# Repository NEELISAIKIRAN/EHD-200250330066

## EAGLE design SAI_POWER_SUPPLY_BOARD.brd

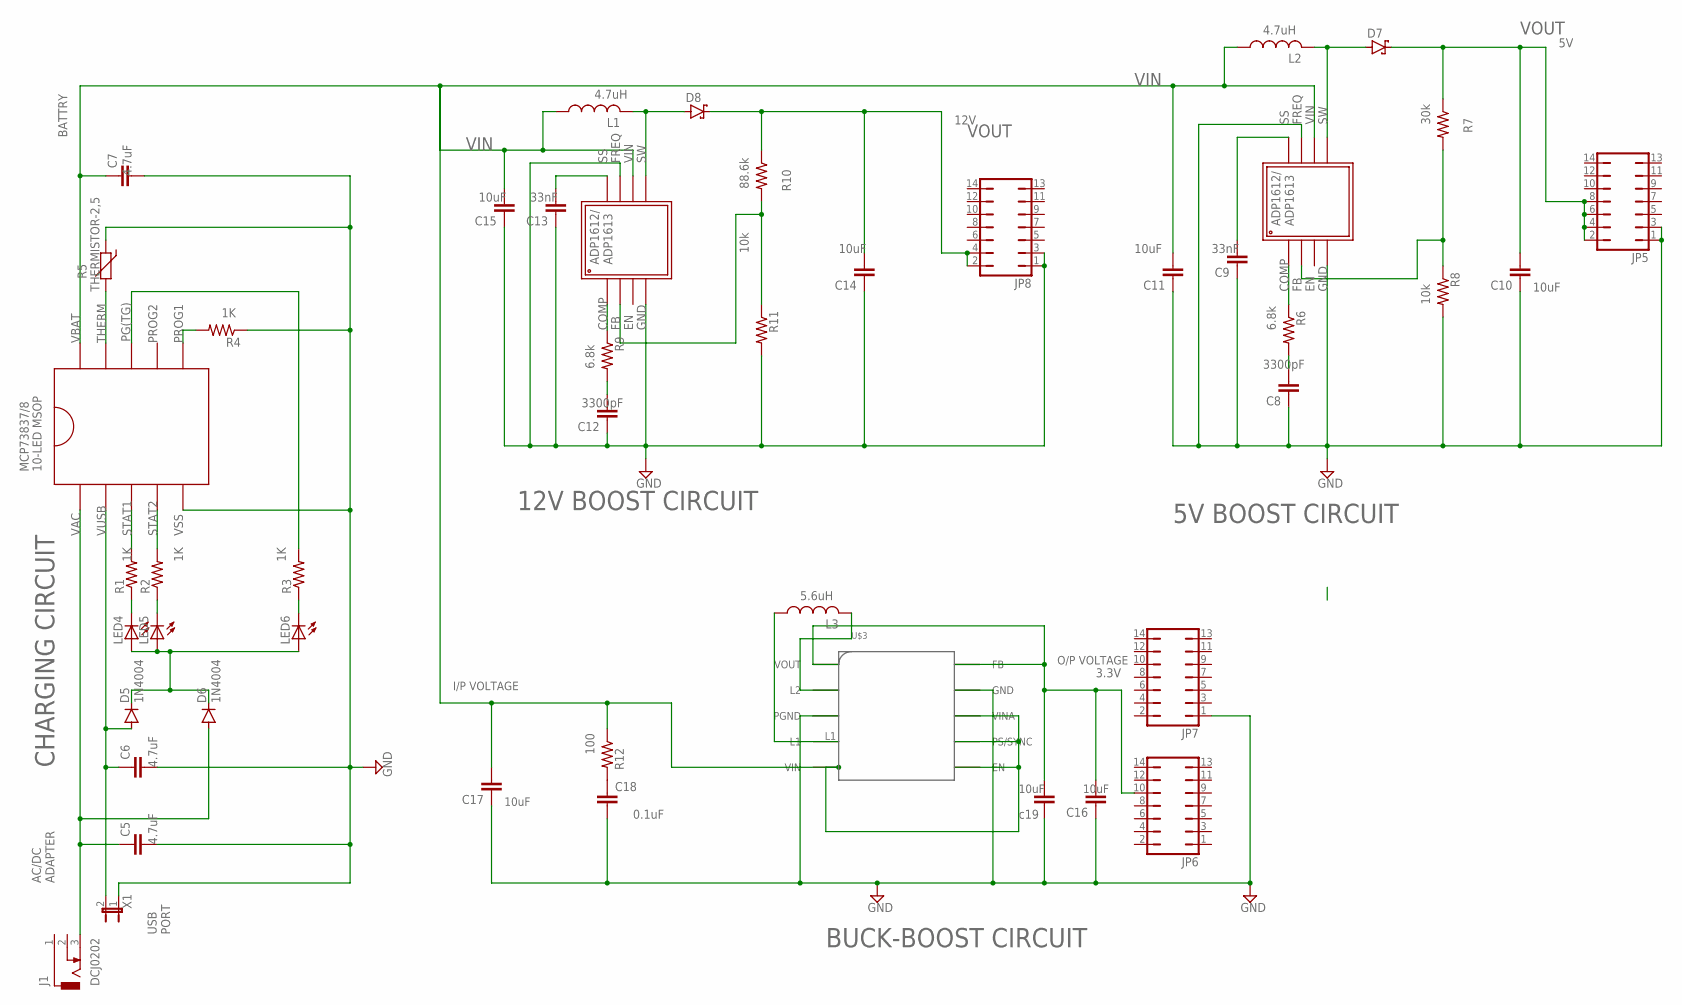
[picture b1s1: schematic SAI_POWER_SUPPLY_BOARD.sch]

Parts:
C1, C8, C9, C10, C11, C12, C13, C14, C15, C16, C17, C18: C2,5-3; C2.5-3
C5, C6, C7: C2.5/5; C2.5-5
D5, D6: 1N4004; DO41-10
D7, D8: SCHOTTKY-DIODEC4111-15; C4111-15
J1: DCJ0202
JP1: JP1E; JP1
JP5, JP6, JP7, JP8: JP7Q
L1, L2, L3: L-US0204/5; 0204/5
LED4, LED5, LED6: LED3MM
R1, R2, R3, R4, R6, R7, R8, R9, R10, R11, R12: R-US_0204/2V; 0204V
R5: THERMISTOR-2,5; RS-2,5
U$1, U$2: ADP1612
U$3: TPS63002
U$4: MCP73837/8

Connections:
GND: C1.1, C5.2, C6.2, C7.2, C8.1, C9.1, C10.1, C11.1, C12.1, C13.1, C14.1, C15.1, C16.1, C17.1, C18.2, JP1.1, JP5.1, JP5.3, JP7.1, JP8.1, JP8.3, R4.1, R5.1, R8.2, R11.2, U$1.P$4, U$1.P$6, U$2.P$4, U$2.P$6, U$3.GND, U$3.PGND, U$4.P$5
unnamed: C10.2, D7.C, JP5.2, JP5.4, JP5.6, JP5.8, R7.1
unnamed: L3.1, U$3.L1
unnamed: C7.1, C11.2, C15.2, C17.2, L1.1, L2.1, R12.1, U$1.P$7, U$2.P$7, U$3.EN, U$3.PS/SYNC, U$3.VIN, U$3.VINA, U$4.P$10
unnamed: C1.2, C16.2, JP6.10, U$3.FB, U$3.VOUT
unnamed: L3.2, U$3.L2
unnamed: C18.1, R12.2
unnamed: C5.1, D6.A, J1.3, U$4.P$1
unnamed: C14.2, D8.C, JP8.2, JP8.4, R10.1
unnamed: C6.1, D5.A, JP1.2, U$4.P$2
unnamed: D5.C, D6.C, LED4.A, LED5.A, LED6.A
unnamed: R4.2, U$4.P$6
unnamed: R5.2, U$4.P$9
unnamed: LED4.K (C), R1.1
unnamed: R1.2, U$4.P$3
unnamed: R2.2, U$4.P$4
unnamed: LED5.K (C), R2.1
unnamed: LED6.K (C), R3.1
unnamed: R3.2, U$4.P$8
unnamed: D7.A, L2.2, U$1.P$8
unnamed: R6.1, U$1.P$1
unnamed: C8.2, R6.2
unnamed: R7.2, R8.1, U$1.P$2
unnamed: C9.2, U$1.P$5
unnamed: D8.A, L1.2, U$2.P$8
unnamed: R9.1, U$2.P$1
unnamed: C12.2, R9.2
unnamed: R10.2, R11.1, U$2.P$2
unnamed: C13.2, U$2.P$5

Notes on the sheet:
AC/DC ADAPTER
USB PORT
BATTRY
CHARGING CIRCUIT
VIN
VOUT
5V BOOST CIRCUIT
12V BOOST CIRCUIT
10uF
30k
10k
4.7uH
33nF
6.8k
3300pF
88.6k
BUCK-BOOST CIRCUIT
I/P VOLTAGE
O/P VOLTAGE
5.6uH
c19
3.3V
12V
100
0.1uF
4.7uF

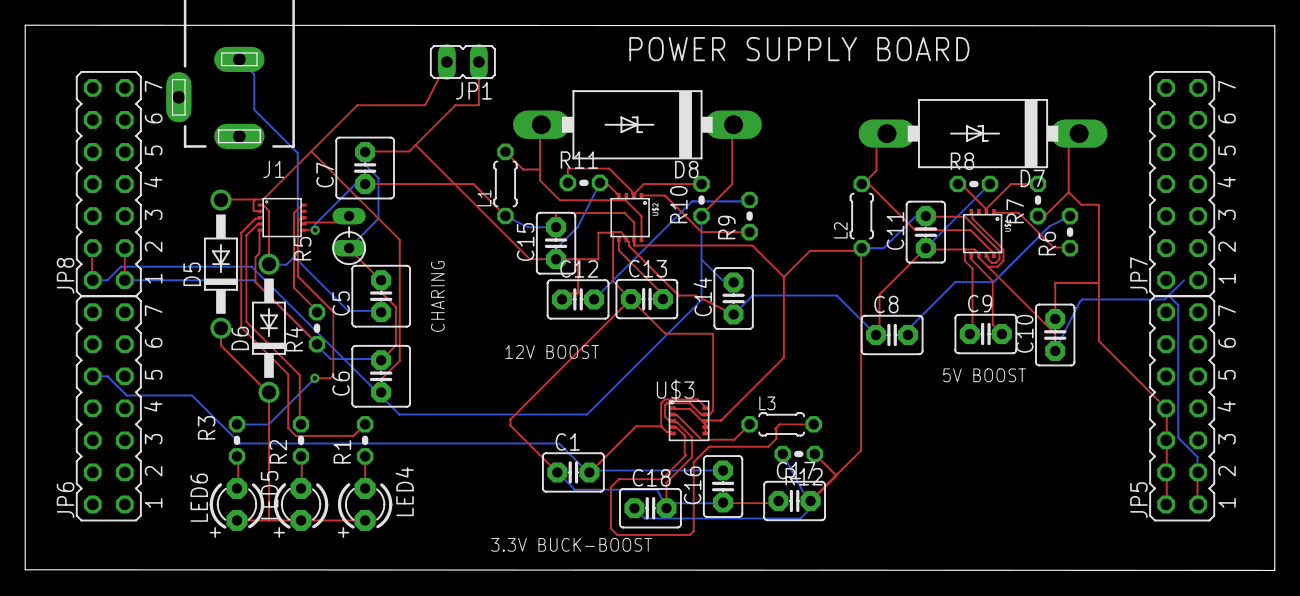
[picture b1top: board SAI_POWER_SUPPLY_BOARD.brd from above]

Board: 2 copper layers, 99.1 x 43.2 mm, 47 parts (0 on the bottom side), 29 nets.

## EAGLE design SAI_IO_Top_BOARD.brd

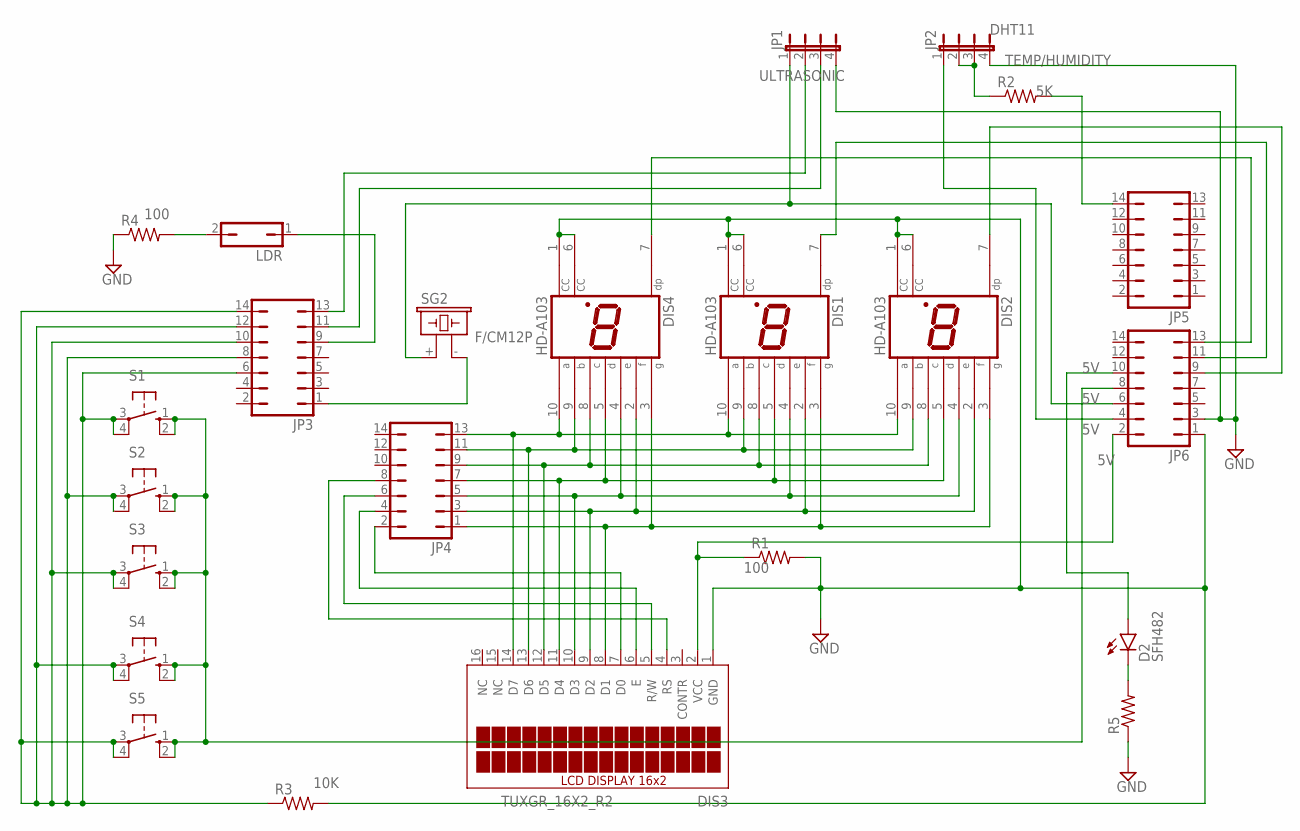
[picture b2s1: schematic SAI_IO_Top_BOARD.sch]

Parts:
D2: SFH482
DIS1, DIS2, DIS4: HD-A103; HDSP-A
DIS3: TUXGR_16X2_R2
JP1, JP2: JP4E; JP4
JP3, JP4, JP5, JP6: JP7Q
LDR: JP1Q; JP1
R1, R2, R3, R4, R5: R-US_0204/2V; 0204V
S1, S2, S3, S4, S5: 10-XX; B3F-10XX
SG2: F/CM12P

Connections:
5V: JP1.1, JP6.6, SG2.+ (1)
GND: DIS1.1 (CC), DIS1.6 (CC), DIS2.1 (CC), DIS2.6 (CC), DIS3.1 (GND), DIS4.1 (CC), DIS4.6 (CC), JP1.4, JP2.4, JP6.1, JP6.3, R1.2, R3.2, R4.1, R5.1; also elsewhere on the board
unnamed: JP3.1, SG2.- (2)
unnamed: JP2.2, JP2.3, R2.1
unnamed 6: DIS1.3 (G), DIS2.3 (G), DIS3.8 (D1), DIS4.3 (G), JP4.1; also elsewhere on the board
unnamed 7: DIS1.2 (F), DIS2.2 (F), DIS3.9 (D2), DIS4.2 (F), JP4.3; also elsewhere on the board
unnamed 8: DIS1.4 (E), DIS2.4 (E), DIS3.10 (D3), DIS4.4 (E), JP4.5; also elsewhere on the board
unnamed 9: DIS1.5 (D), DIS2.5 (D), DIS3.11 (D4), DIS4.5 (D), JP4.7; also elsewhere on the board
unnamed 10: DIS1.8 (C), DIS2.8 (C), DIS3.12 (D5), DIS4.8 (C), JP4.9; also elsewhere on the board
unnamed 11: DIS1.9 (B), DIS2.9 (B), DIS3.13 (D6), DIS4.9 (B), JP4.11; also elsewhere on the board
unnamed 12: DIS1.10 (A), DIS2.10 (A), DIS3.14 (D7), DIS4.10 (A), JP4.13; also elsewhere on the board
unnamed 13: DIS3.7 (D0), JP4.2; also elsewhere on the board
unnamed 14: DIS3.2 (VCC), JP6.2, R1.1; also elsewhere on the board
unnamed: JP1.3, JP3.11
unnamed 16: DIS3.6 (E), JP4.4; also elsewhere on the board
unnamed 17: DIS3.5 (R/W), JP4.6; also elsewhere on the board
unnamed 18: DIS3.4 (RS), JP4.8; also elsewhere on the board
unnamed: JP3.6, JP3.8, JP3.10, JP3.12, JP3.14, R3.1, S1.3, S1.4 (P1), S2.3, S2.4 (P1), S3.3, S3.4 (P1), S4.3, S4.4 (P1), S5.3, S5.4 (P1)
unnamed: JP1.2, JP3.13
unnamed: JP5.14, R2.2
unnamed: JP3.9, LDR.1
unnamed: LDR.2, R4.2
unnamed: JP2.1, JP6.4
unnamed: JP6.8, S1.1 (S), S1.2 (S1), S2.1 (S), S2.2 (S1), S3.1 (S), S3.2 (S1), S4.1 (S), S4.2 (S1), S5.1 (S), S5.2 (S1)
unnamed: D2.K (C), R5.2
unnamed: D2.A, JP6.10
unnamed: DIS4.7 (DP), JP6.13
unnamed: DIS1.7 (DP), JP6.11
unnamed: DIS2.7 (DP), JP6.9

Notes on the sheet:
100
ULTRASONIC
TEMP/HUMIDITY
DHT11
10K

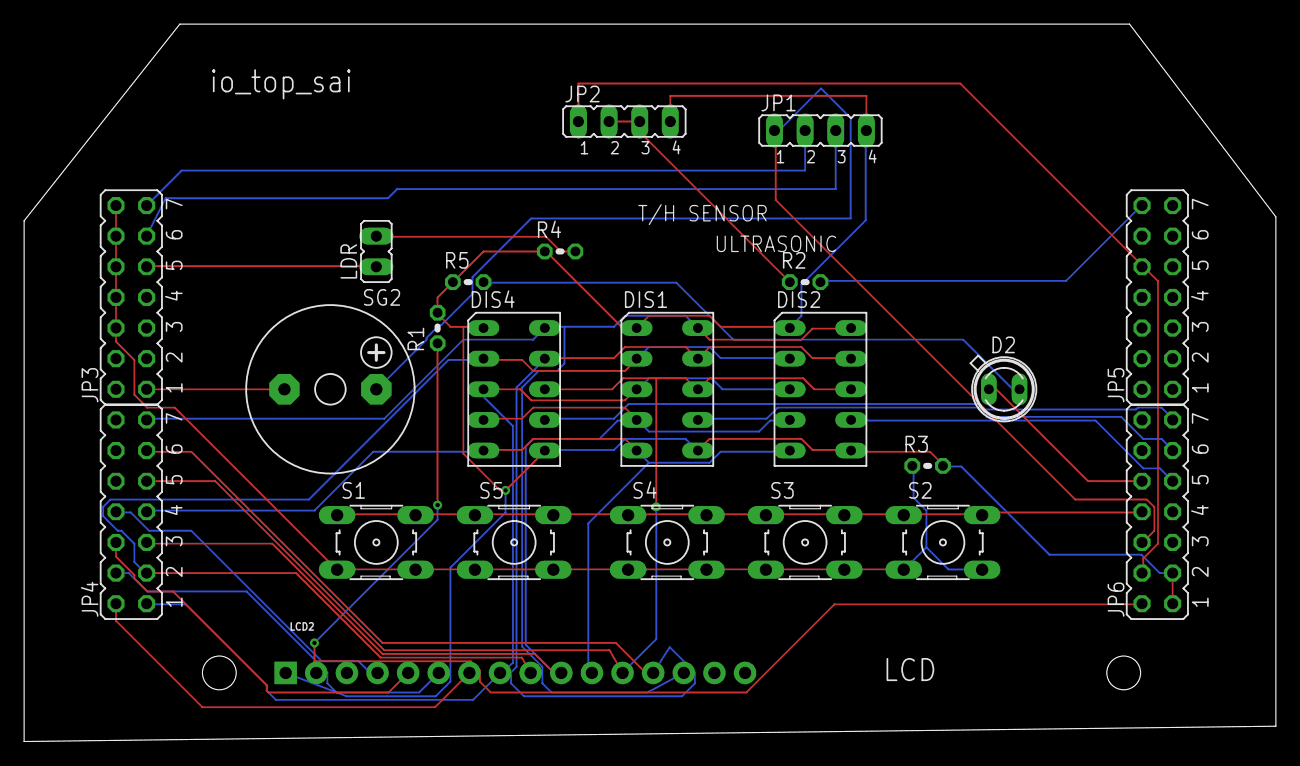
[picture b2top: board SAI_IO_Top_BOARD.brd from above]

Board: 2 copper layers, 103.8 x 59.5 mm, 23 parts (0 on the bottom side), 29 nets.

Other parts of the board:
LCD2: LCD-16X2NOSILK; LCD-16X2_NOSILK

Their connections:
GND: LCD2.1; also elsewhere on the board
unnamed 6: LCD2.8; also elsewhere on the board
unnamed 7: LCD2.9; also elsewhere on the board
unnamed 8: LCD2.10; also elsewhere on the board
unnamed 9: LCD2.11; also elsewhere on the board
unnamed 10: LCD2.12; also elsewhere on the board
unnamed 11: LCD2.13; also elsewhere on the board
unnamed 12: LCD2.14; also elsewhere on the board
unnamed 13: LCD2.7; also elsewhere on the board
unnamed 14: LCD2.2; also elsewhere on the board
unnamed 16: LCD2.6; also elsewhere on the board
unnamed 17: LCD2.5; also elsewhere on the board
unnamed 18: LCD2.4; also elsewhere on the board

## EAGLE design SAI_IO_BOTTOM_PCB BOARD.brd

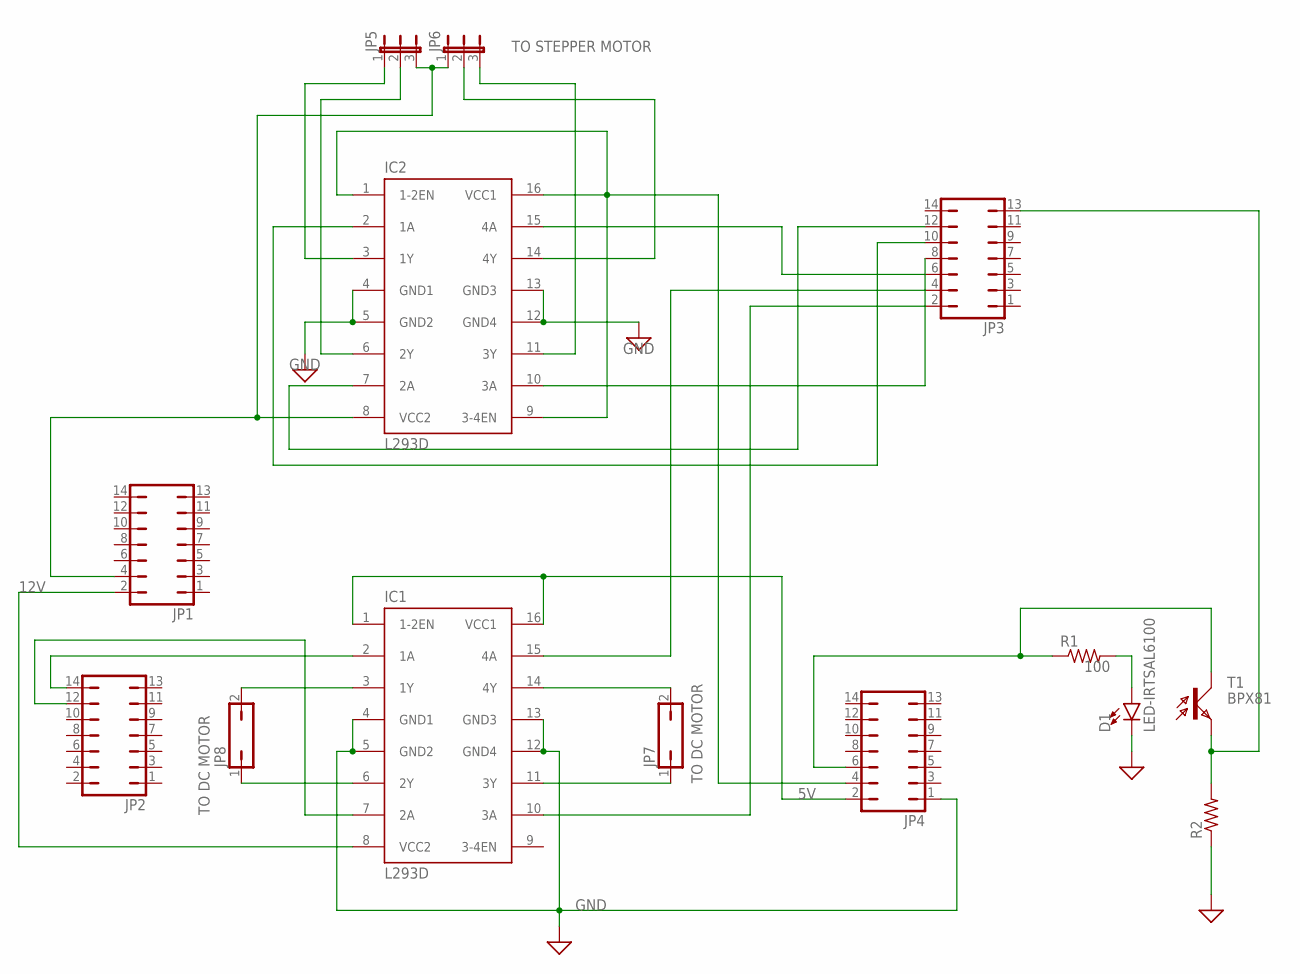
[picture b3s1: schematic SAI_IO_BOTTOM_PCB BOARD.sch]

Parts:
D1: LED-IRTSAL6100; LED_5MM
IC1, IC2: L293D; DIL16
JP1, JP2, JP3, JP4: JP7Q
JP5, JP6: JP2E; JP2
JP7, JP8: JP1Q; JP1
R1, R2: R-US_0204/2V; 0204V
T1: BPX81

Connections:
5V: IC1.8 (VCC2), JP1.2
GND: D1.K (C), IC1.4 (GND1), IC1.5 (GND2), IC1.12 (GND4), IC1.13 (GND3), IC2.4 (GND1), IC2.5 (GND2), IC2.12 (GND4), IC2.13 (GND3), JP4.1, R2.1
unnamed: IC1.3 (1Y), JP8.2
unnamed: IC1.6 (2Y), JP8.1
unnamed: IC1.11 (3Y), JP7.1
unnamed: IC1.14 (4Y), JP7.2
unnamed: IC1.2 (1A), JP2.14
unnamed: IC1.7 (2A), JP2.12
unnamed: IC1.1 (1-2EN), IC1.16 (VCC1), JP4.2
unnamed: IC1.15 (4A), JP3.4
unnamed: IC1.10 (3A), JP3.2
unnamed: IC2.15 (4A), JP3.6
unnamed: IC2.10 (3A), JP3.8
unnamed: IC2.2 (1A), JP3.10
unnamed: IC2.7 (2A), JP3.12
unnamed: IC2.1 (1-2EN), IC2.9 (3-4EN), IC2.16 (VCC1), JP4.4
unnamed: IC2.6 (2Y), JP5.2
unnamed: IC2.3 (1Y), JP5.1
unnamed: IC2.11 (3Y), JP6.3
unnamed: IC2.8 (VCC2), JP1.4, JP5.3, JP6.1
unnamed: IC2.14 (4Y), JP6.2
unnamed: D1.A, R1.2
unnamed: JP3.13, R2.2, T1.E
unnamed: JP4.6, R1.1, T1.C

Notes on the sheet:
12V
GND
TO STEPPER MOTOR
TO DC MOTOR
100

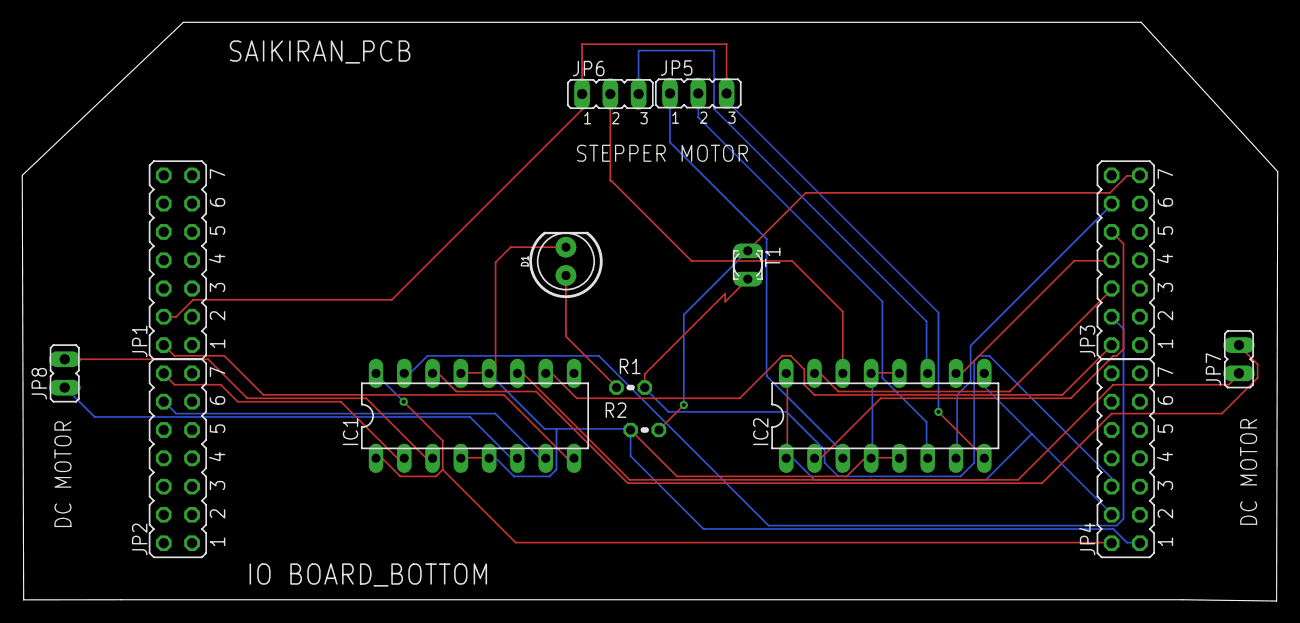
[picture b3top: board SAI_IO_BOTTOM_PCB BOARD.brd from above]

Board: 2 copper layers, 112.7 x 52.0 mm, 14 parts (0 on the bottom side), 24 nets.

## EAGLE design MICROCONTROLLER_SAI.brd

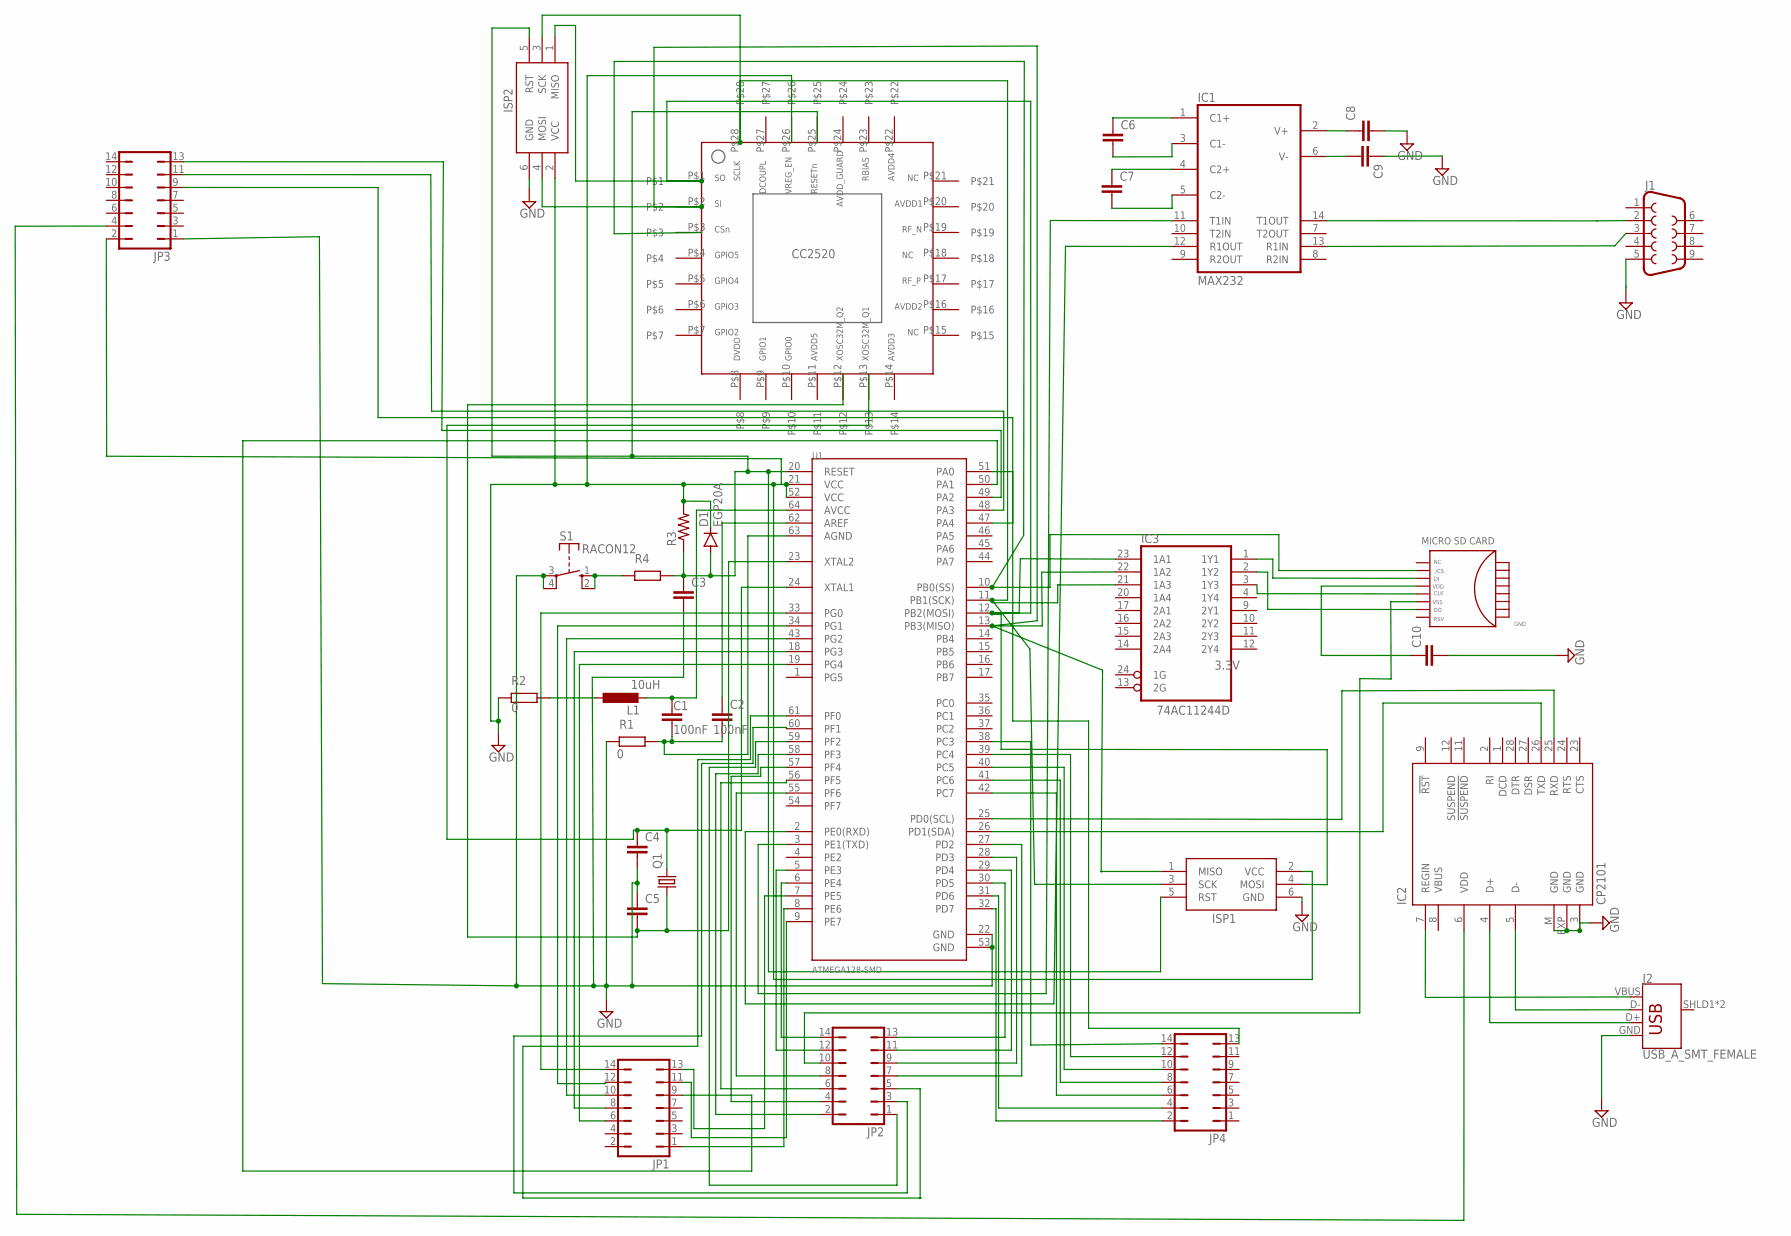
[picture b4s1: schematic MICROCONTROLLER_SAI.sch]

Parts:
C1, C2, C4, C5: C2,5-3; C2.5-3
C3, C6, C7, C8, C9, C10: C7.5/3; C7.5B3
D1: EGP20A; DO15-12
IC1: MAX232; DIL16
IC2: CP2101; MLP28
IC3: 74AC11244D; SO24W
ISP1, ISP2: AVRISP-6; AVRISP
J1: DB9FEMALE; DB9
J2: USB_A_SMT_FEMALE; USB-A-S-SILK-FEMALE
JP1, JP2, JP3, JP4: JP7Q
L1: L-EU0204/5; 0204/5
Q1: CRYSTALHC49U-V; HC49U-V
R3: R-US_VTA55; VTA55
S1: RACON12
U1: ATMEGA128-SMD; TQFP64_14X14MM
U$1: SD-CARD
U$2: CC2520

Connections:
3.3V: C10.1, U$1.P$4
5V: C3.2, C4.2, C5.1, D1.C, IC1.15 (GND), IC3.5 (GND), IC3.6 (GND), IC3.7 (GND), IC3.8 (GND), ISP1.2 (VCC), ISP2.2 (VCC), JP3.1, JP3.2, R3.2, S1.3, S1.4, U1.21 (VCC), U1.22 (GND), U1.52 (VCC), U1.53 (GND), U$2.P$26
GND: C8.2, C9.1, C10.2, IC2.3 (GND), IC2.EXP (GND), IC2.M (GND), ISP1.6 (GND), ISP2.6 (GND), J1.5, J2.GND
unnamed: C2.1, U1.62 (AREF)
unnamed: C1.2, C2.2, U1.63 (AGND)
unnamed: C1.1, L1.2, U1.64 (AVCC)
unnamed: S1.1 (S), S1.2 (S)
unnamed: C6.1, IC1.1 (C1+)
unnamed: U1.10 (PB0(SS)), U$1.P$2, U$2.P$3
unnamed: C4.1, Q1.2, U1.24 (XTAL1), U$2.P$13
unnamed: C5.2, Q1.1, U1.23 (XTAL2), U$2.P$12
unnamed: IC3.22 (1A2), ISP1.1 (MISO), ISP2.4 (MOSI), U1.13 (PB3(MISO)), U$2.P$2
unnamed: IC3.23 (1A1), ISP1.4 (MOSI), ISP2.1 (MISO), U1.12 (PB2(MOSI)), U$2.P$1
unnamed: IC3.21 (1A3), ISP1.3 (SCK), ISP2.3 (SCK), U1.11 (PB1(SCK)), U$2.P$28
unnamed: C9.2, IC1.6 (V-)
unnamed: C8.1, IC1.2 (V+)
unnamed: C7.1, IC1.4 (C2+)
unnamed: C6.2, IC1.3 (C1-)
unnamed: C7.2, IC1.5 (C2-)
unnamed: IC2.25 (RXD), U1.25 (PD0(SCL))
unnamed: IC1.11 (T1IN), U1.3 (PE1(TXD))
unnamed: IC1.12 (R1OUT), U1.2 (PE0(RXD))
unnamed: IC3.3 (1Y3), U$1.P$5
unnamed: JP2.5, U1.61 (PF0)
unnamed: IC2.5 (D-), J2.D-
unnamed: JP2.3, U1.60 (PF1)
unnamed: IC2.4 (D+), J2.D+
unnamed: IC2.7 (REGIN), J2.VBUS
unnamed: IC1.14 (T1OUT), J1.2
unnamed: IC1.13 (R1IN), J1.3
unnamed: C3.1, D1.A, ISP1.5 (RST), ISP2.5 (RST), R3.1, U1.20 (RESET), U$2.P$25
unnamed: IC2.26 (TXD), U1.26 (PD1(SDA))
unnamed: IC3.1 (1Y1), U$1.P$3
unnamed: IC3.2 (1Y2), U$1.P$7
unnamed: JP2.12, U1.5 (PE3)
unnamed: JP2.14, U1.6 (PE4)
unnamed: JP4.2, U1.32 (PD7)
unnamed: JP4.4, U1.31 (PD6)
unnamed: JP4.12, U1.39 (PC4)
unnamed: JP4.10, U1.40 (PC5)
unnamed: JP4.8, U1.41 (PC6)
unnamed: JP4.6, U1.42 (PC7)
unnamed: JP4.13, U1.51 (PA0)
unnamed: JP1.11, U1.9 (PE7)
unnamed: JP1.1, U1.8 (PE6)
unnamed: JP1.13, U1.7 (PE5)
unnamed: JP1.9, U1.50 (PA1)
unnamed: JP4.14, U1.38 (PC3)
unnamed: JP1.14, U1.33 (PG0)
unnamed: JP1.12, U1.34 (PG1)
unnamed: JP1.10, U1.43 (PG2)
unnamed: JP1.8, U1.18 (PG3)
unnamed: JP1.6, U1.19 (PG4)
unnamed: JP2.13, U1.30 (PD5)
unnamed: JP2.11, U1.29 (PD4)
unnamed: JP2.9, U1.28 (PD3)
unnamed: JP2.7, U1.27 (PD2)
unnamed: JP2.1, U1.59 (PF2)
unnamed: JP2.2, U1.58 (PF3)
unnamed: JP2.4, U1.57 (PF4)
unnamed: JP2.6, U1.56 (PF5)
unnamed: JP2.8, U1.55 (PF6)
unnamed: JP2.10, U$1.P$6
unnamed: JP3.13, U1.49 (PA2)
unnamed: JP3.11, U1.48 (PA3)
unnamed: JP3.9, U1.47 (PA4)
unnamed: IC2.6 (VDD), JP3.4
VCC: IC1.16 (VCC), IC3.18 (VCC), IC3.19 (VCC)

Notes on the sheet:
100nF
10uH

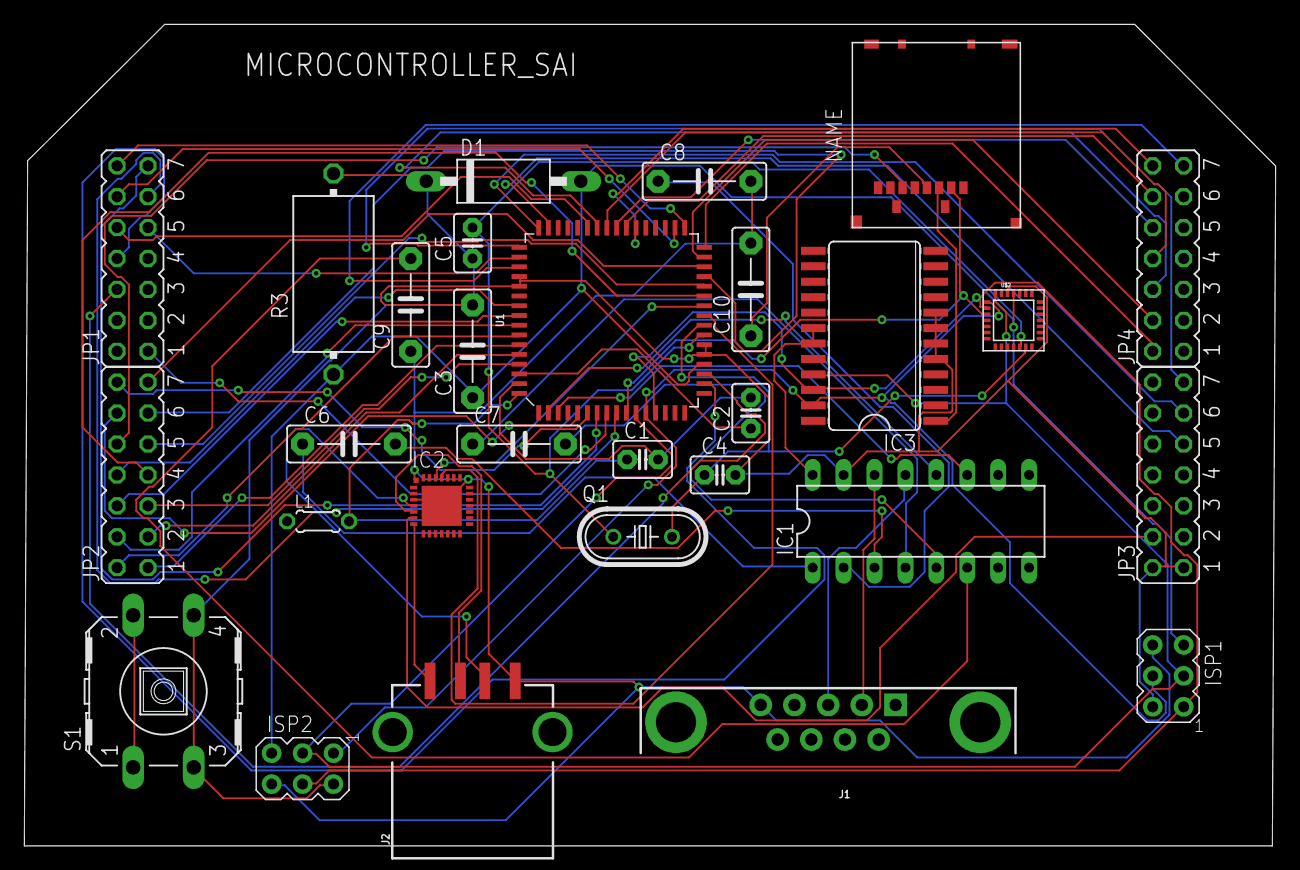
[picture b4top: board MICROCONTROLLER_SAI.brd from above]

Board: 2 copper layers, 102.8 x 67.5 mm, 29 parts (0 on the bottom side), 68 nets.

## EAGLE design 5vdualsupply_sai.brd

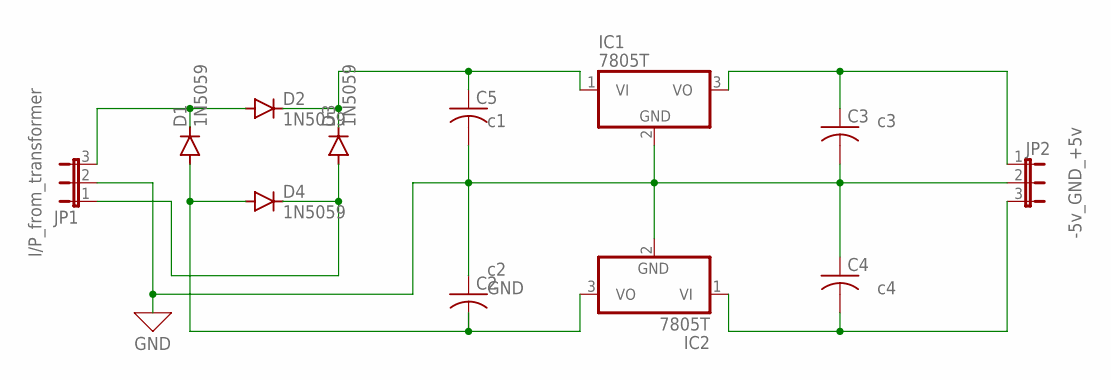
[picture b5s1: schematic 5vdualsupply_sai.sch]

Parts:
C2, C3, C4, C5: C-US025-024X044; C025-024X044
D1, D2, D3, D4: 1N5059; DO204-10
IC1, IC2: 7805T; TO220H
JP1, JP2: JP2W

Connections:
GND: C2.1, C3.2, C4.1, C5.2, IC1.2 (GND), IC2.2 (GND), JP1.2, JP2.2
unnamed: D3.A, D4.C, JP1.1
unnamed: C2.2, D1.A, D4.A, IC2.3 (VO)
unnamed: D1.C, D2.A, JP1.3
unnamed: C3.1, IC1.3 (VO), JP2.1
unnamed: C5.1, D2.C, D3.C, IC1.1 (VI)
unnamed: C4.2, IC2.1 (VI), JP2.3

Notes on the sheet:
I/P_from_transformer
-5v_GND_+5v

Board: 2 copper layers, 12 parts (0 on the bottom side), 7 nets, no tracks yet.

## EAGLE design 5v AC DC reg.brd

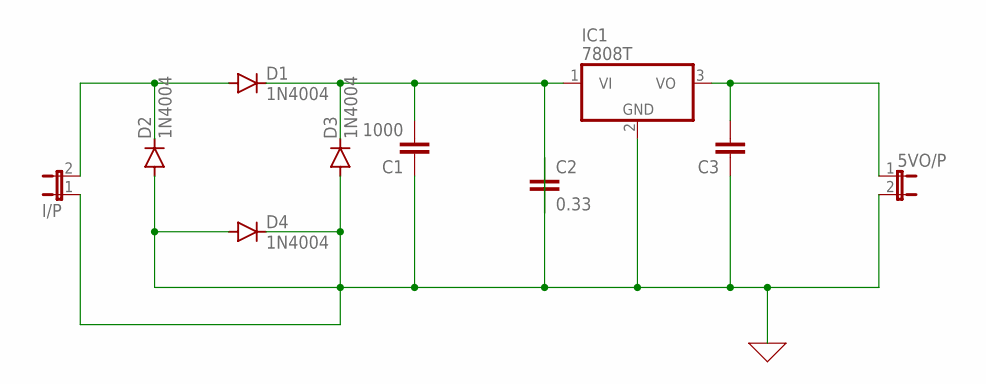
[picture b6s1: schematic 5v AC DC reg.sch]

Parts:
5VO/P: JP1E; JP1
C1: 1000; C2.5-3
C2: 0.33; C2.5-3
C3: C2,5-3; C2.5-3
D1, D2, D3, D4: 1N4004; DO41-10
I/P: JP1E; JP1
IC1: 7808T; TO220H

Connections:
0: 5VO/P.2, C1.1, C2.1, C3.1, D2.A, D3.A, D4.A, D4.C, I/P.1, IC1.2 (GND)
unnamed: D1.A, D2.C, I/P.2
unnamed: C1.2, C2.2, D1.C, D3.C, IC1.1 (VI)
unnamed: 5VO/P.1, C3.2, IC1.3 (VO)

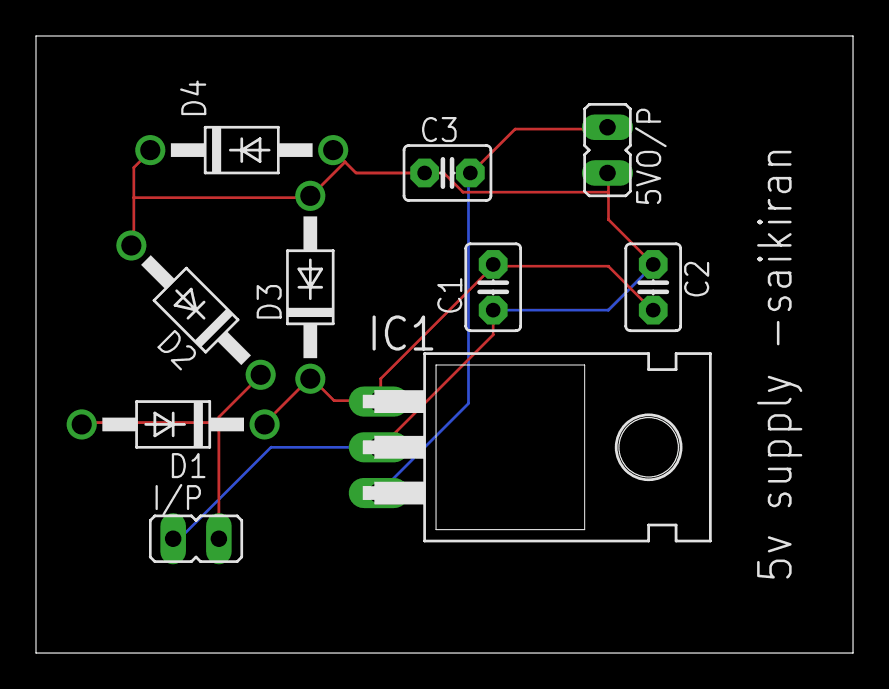
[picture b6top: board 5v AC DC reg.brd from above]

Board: 2 copper layers, 45.4 x 34.3 mm, 10 parts (0 on the bottom side), 4 nets.

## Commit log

2021-02-03 cdac sample

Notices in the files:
parts and their libraries:
SparkFun-Connectors: Licensing: Creative Commons ShareAlike 4.0 International - https://creativecommons.org/licenses/by-sa/4.0
